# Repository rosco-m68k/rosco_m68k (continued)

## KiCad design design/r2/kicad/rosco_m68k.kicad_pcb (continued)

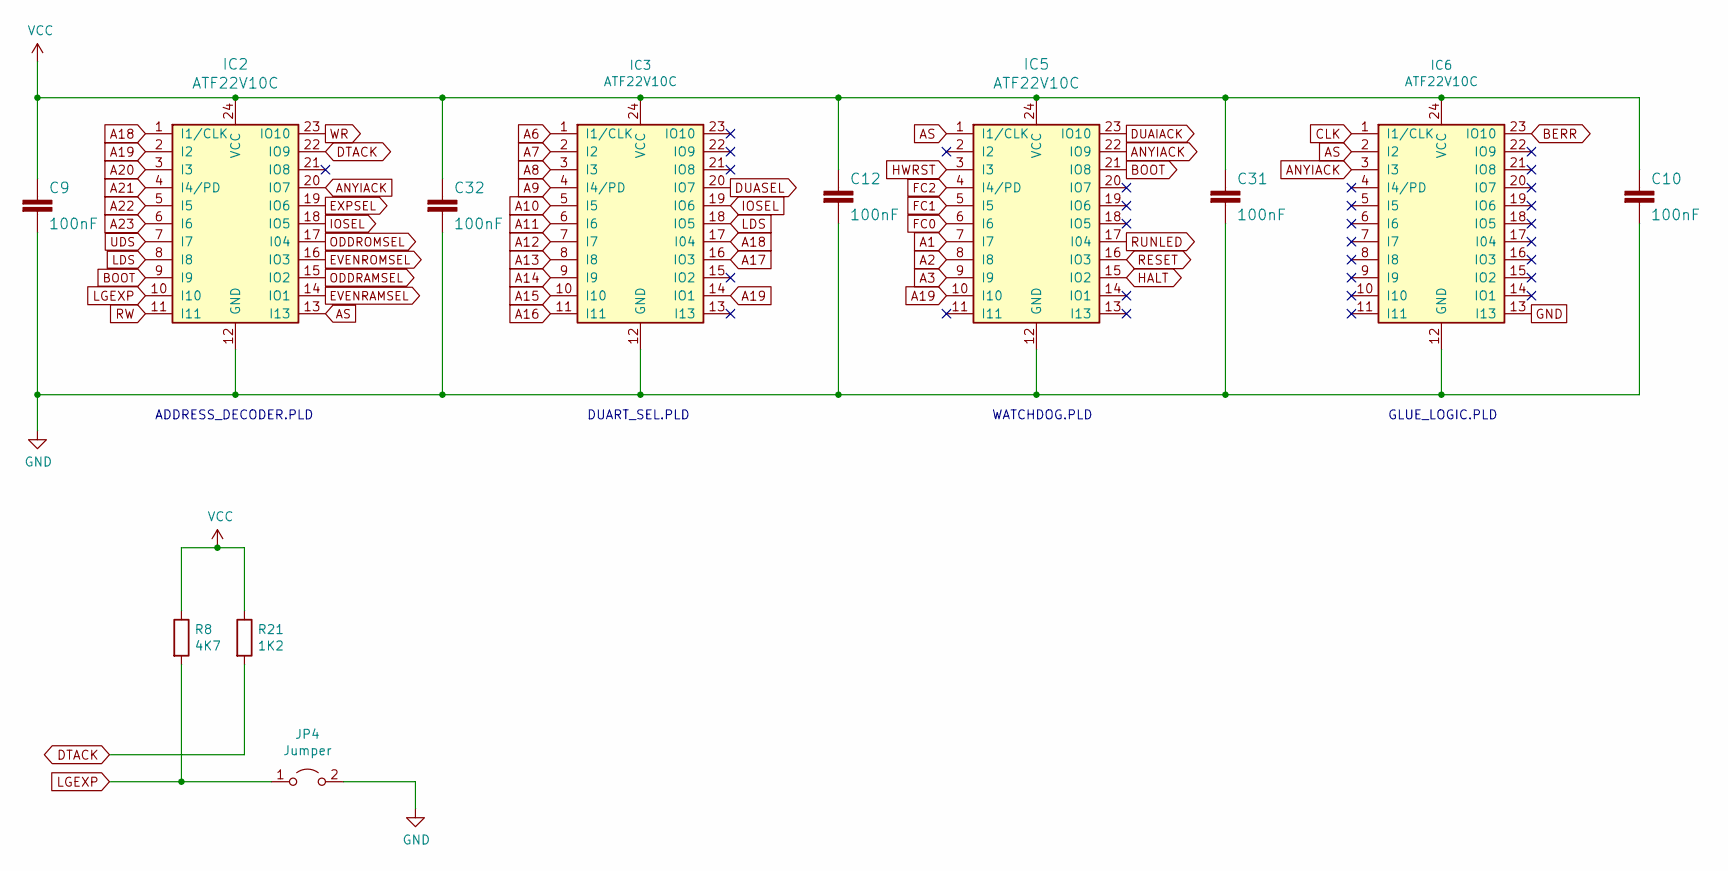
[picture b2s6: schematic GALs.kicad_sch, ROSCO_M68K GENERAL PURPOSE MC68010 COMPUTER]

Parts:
C9, C10, C12, C31, C32: 100nF; C2.5-3
IC2, IC3, IC5, IC6: ATF22V10C; DIP-24_W7.62mm_Socket_LongPads
JP4: Jumper; 1X02
R8: 4K7; 0207_10
R21: 1K2; 0207_10

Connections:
A1: IC5.7 (I7); also elsewhere on the board
A2: IC5.8 (I8); also elsewhere on the board
A3: IC5.9 (I9); also elsewhere on the board
A6: IC3.1 (I1/CLK); also elsewhere on the board
A7: IC3.2 (I2); also elsewhere on the board
A8: IC3.3 (I3); also elsewhere on the board
A9: IC3.4 (I4/PD); also elsewhere on the board
A10: IC3.5 (I5); also elsewhere on the board
A11: IC3.6 (I6); also elsewhere on the board
A12: IC3.7 (I7); also elsewhere on the board
A13: IC3.8 (I8); also elsewhere on the board
A14: IC3.9 (I9); also elsewhere on the board
A15: IC3.10 (I10); also elsewhere on the board
A16: IC3.11 (I11); also elsewhere on the board
A17: IC3.16 (IO3); also elsewhere on the board
A18: IC2.1 (I1/CLK), IC3.17 (I04); also elsewhere on the board
A19: IC2.2 (I2), IC3.14 (IO1), IC5.10 (I10); also elsewhere on the board
A20: IC2.3 (I3); also elsewhere on the board
A21: IC2.4 (I4/PD); also elsewhere on the board
A22: IC2.5 (I5); also elsewhere on the board
A23: IC2.6 (I6); also elsewhere on the board
ANYIACK: IC2.20 (IO7), IC5.22 (IO9), IC6.3 (I3)
AS: IC2.13 (I13), IC5.1 (I1/CLK), IC6.2 (I2); also elsewhere on the board
BERR: IC6.23 (IO10); also elsewhere on the board
BOOT: IC2.9 (I9), IC5.21 (IO8)
CLK: IC6.1 (I1/CLK); also elsewhere on the board
DTACK: IC2.22 (IO9), R21.2; also elsewhere on the board
DUAIACK: IC5.23 (IO10); also elsewhere on the board
DUASEL: IC3.20 (IO7); also elsewhere on the board
EVENRAMSEL: IC2.14 (IO1); also elsewhere on the board
EVENROMSEL: IC2.16 (IO3); also elsewhere on the board
EXPSEL: IC2.19 (IO6); also elsewhere on the board
FC0: IC5.6 (I6); also elsewhere on the board
FC1: IC5.5 (I5); also elsewhere on the board
FC2: IC5.4 (I4/PD); also elsewhere on the board
GND: C9.2, C10.2, C12.2, C31.2, C32.2, IC2.12 (GND), IC3.12 (GND), IC5.12 (GND), IC6.12 (GND), IC6.13 (I13), JP4.2 (B); also elsewhere on the board
HALT: IC5.15 (IO2); also elsewhere on the board
HWRST: IC5.3 (I3); also elsewhere on the board
IOSEL: IC2.18 (IO5), IC3.19 (IO6); also elsewhere on the board
LDS: IC2.8 (I8), IC3.18 (IO5); also elsewhere on the board
LGEXP: IC2.10 (I10), JP4.1 (A), R8.2
ODDRAMSEL: IC2.15 (IO2); also elsewhere on the board
ODDROMSEL: IC2.17 (I04); also elsewhere on the board
RESET: IC5.16 (IO3); also elsewhere on the board
RUNLED: IC5.17 (I04); also elsewhere on the board
RW: IC2.11 (I11); also elsewhere on the board
UDS: IC2.7 (I7); also elsewhere on the board
VCC: C9.1, C10.1, C12.1, C31.1, C32.1, IC2.24 (VCC), IC3.24 (VCC), IC5.24 (VCC), IC6.24 (VCC), R8.1, R21.1; also elsewhere on the board
WR: IC2.23 (IO10); also elsewhere on the board

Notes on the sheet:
GLUE_LOGIC.PLD
ADDRESS_DECODER.PLD
DUART_SEL.PLD
WATCHDOG.PLD

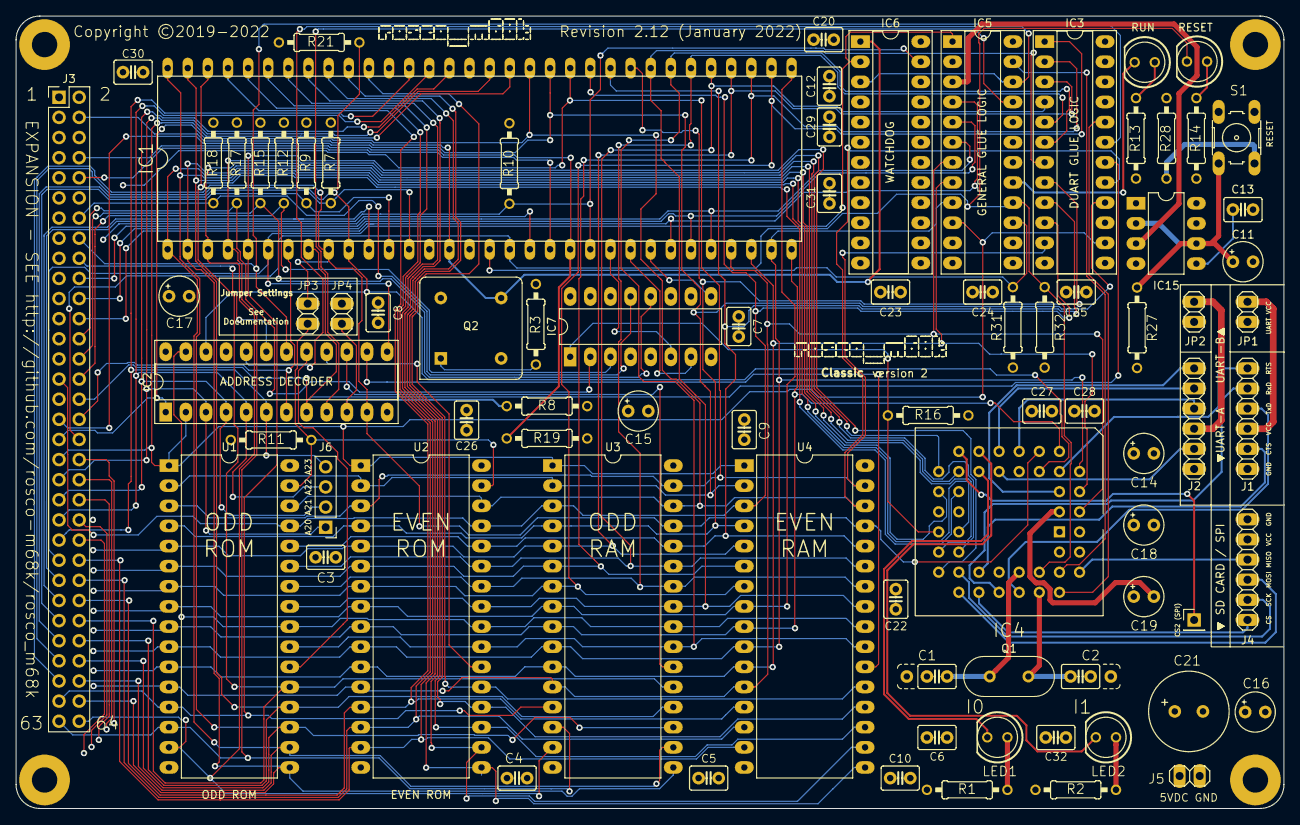
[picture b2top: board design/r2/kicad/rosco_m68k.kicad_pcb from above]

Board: 4 copper layers, 160.0 x 100.0 mm, 88 parts (0 on the bottom side), 109 nets.

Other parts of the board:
OSHW_Mono_0.25_Scale: UK000006; OSHW_Mono_0.25_Scale

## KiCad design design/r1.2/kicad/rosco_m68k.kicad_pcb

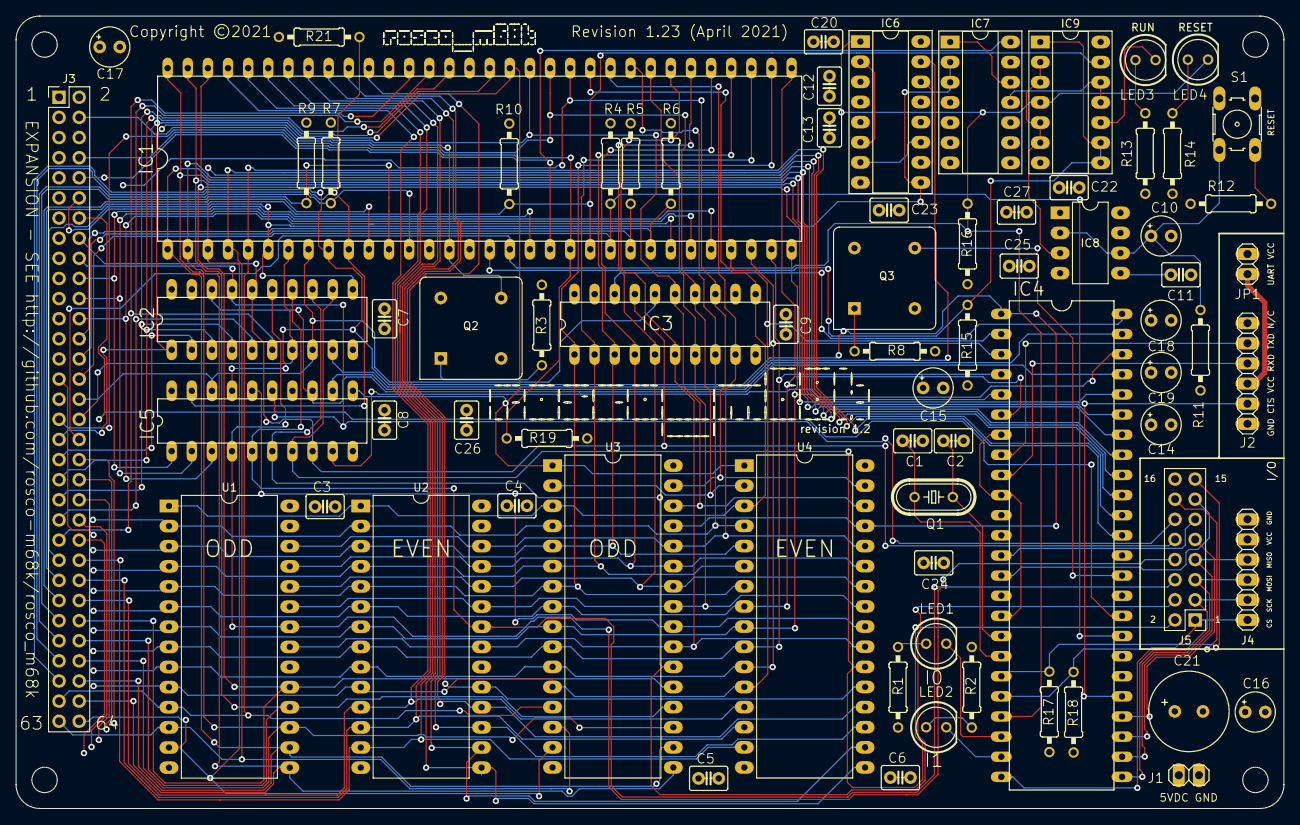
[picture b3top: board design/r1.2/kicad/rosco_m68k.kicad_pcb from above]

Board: 4 copper layers, 160.0 x 100.0 mm, 79 parts (0 on the bottom side), 110 nets.

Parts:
C1, C2: 33pF; C2.5-3
C3, C4, C5, C6, C7, C8, C9, C11, C12, C13, C20, C22, C23, C24, C25, C26, C27: 100nF; C2.5-3
C10, C14, C15, C16, C17, C18, C19: 100uF; E2,5-5
C21: 470uF; E3,5-10
H1, H2, H3, H4: MountingHole; MountingHole_3.2mm_M3
IC1: MC68010P10; DIL64
IC2, IC3, IC5: ATF16V8BQL-15PU; DIL20
IC4: MC68901P; DIL48
IC6: 74174N; DIP-16_W7.62mm_Socket_LongPads
IC7: 74LS93; DIP-14_W7.62mm_Socket_LongPads
IC8: 555N; DIP-8_W7.62mm_LongPads
IC9: 74LS01N; DIP-14_W7.62mm_Socket_LongPads
J1: PWR; 1X02
J2, J4: Conn_01x06; 1X06
J3: Conn_02x32_Odd_Even; PinHeader_2x32_P2.54mm_Vertical
J5: GPIO-PANEL; PinHeader_2x08_P2.54mm_Vertical
JP1: FTDI POWER; 1X02
LED1, LED3: GREEN; LED5MM
LED2, LED4: RED; LED5MM
OSHW_Mono_0.25_Scale: UK000006; OSHW_Mono_0.25_Scale
Q1: 3.6864MHz; HC49_S
Q2: 5H8ET-10.000; Oscillator_DIP-8
Q3: 5H8ET-4.000; Oscillator_DIP-8
R1, R2, R13, R14: 330R; 0207_10
R3, R4, R5, R6, R7, R8, R9, R10, R15, R16, R17, R18: 4K7; 0207_10
R11, R21: 2K2; 0207_10
R12: 270R; 0207_10
R19: 10K; 0207_10
S1: 10-XX; B3F-10XX
U1, U2: AT28C256-15PU; DIP-28_W15.24mm_LongPads
U3, U4: AS6C4008-55PCN; DIP-32_W15.24mm_LongPads

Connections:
/Expansion/A1: IC1.29, IC4.2, J3.1, U1.10, U2.10, U3.12, U4.12
/Expansion/A2: IC1.30, IC4.3, J3.3, U1.9, U2.9, U3.11, U4.11
/Expansion/A3: IC1.31, IC4.4, J3.5, U1.8, U2.8, U3.10, U4.10
/Expansion/A4: IC1.32, IC4.5, J3.7, U1.7, U2.7, U3.9, U4.9
/Expansion/A5: IC1.33, IC4.6, J3.9, U1.6, U2.6, U3.8, U4.8
/Expansion/A6: IC1.34, IC3.1, J3.11, U1.5, U2.5, U3.7, U4.7
/Expansion/A7: IC1.35, IC3.2, J3.13, U1.4, U2.4, U3.6, U4.6
/Expansion/A8: IC1.36, IC3.3, J3.15, U1.3, U2.3, U3.5, U4.5
/Expansion/A9: IC1.37, IC3.4, J3.17, U1.25, U2.25, U3.27, U4.27
/Expansion/A10: IC1.38, IC3.5, J3.19, U1.24, U2.24, U3.26, U4.26
/Expansion/A11: IC1.39, IC3.6, J3.21, U1.21, U2.21, U3.23, U4.23
/Expansion/A12: IC1.40, IC3.7, J3.23, U1.23, U2.23, U3.25, U4.25
/Expansion/A13: IC1.41, IC3.8, J3.25, U1.2, U2.2, U3.4, U4.4
/Expansion/A14: IC1.42, IC3.9, J3.27, U1.26, U2.26, U3.28, U4.28
/Expansion/A15: IC1.43, IC3.11, J3.29, U1.1, U2.1, U3.3, U4.3
/Expansion/A16: IC1.44, IC3.13, J3.31, U3.31, U4.31
/Expansion/A17: IC1.45, IC3.14, J3.33, U3.2, U4.2
/Expansion/A18: IC1.46, IC2.1, IC3.15, J3.35, U3.30, U4.30
/Expansion/A19: IC1.47, IC2.2, IC5.11, J3.37, U3.1, U4.1
/Expansion/A20: IC1.48, IC2.3, J3.39
/Expansion/A21: IC1.50, IC2.4, J3.41
/Expansion/A22: IC1.51, IC2.5, J3.43
/Expansion/A23: IC1.52, IC2.6, J3.45
/Expansion/D0: IC1.5, IC4.37, J3.61, U1.11, U3.13
/Expansion/D1: IC1.4, IC4.38, J3.63, U1.12, U3.14
/Expansion/D2: IC1.3, IC4.39, J3.64, U1.13, U3.15
/Expansion/D3: IC1.2, IC4.40, J3.62, U1.15, U3.17
/Expansion/D4: IC1.1, IC4.41, J3.60, U1.16, U3.18
/Expansion/D5: IC1.64, IC4.42, J3.58, U1.17, U3.19
/Expansion/D6: IC1.63, IC4.43, J3.56, U1.18, U3.20
/Expansion/D7: IC1.62, IC4.44, J3.54, U1.19, U3.21
/Expansion/D8: IC1.61, J3.52, U2.11, U4.13
/Expansion/D9: IC1.60, J3.50, U2.12, U4.14
/Expansion/D10: IC1.59, J3.48, U2.13, U4.15
/Expansion/D11: IC1.58, J3.46, U2.15, U4.17
/Expansion/D12: IC1.57, J3.44, U2.16, U4.18
/Expansion/D13: IC1.56, J3.42, U2.17, U4.19
/Expansion/D14: IC1.55, J3.40, U2.18, U4.20
/Expansion/D15: IC1.54, J3.38, U2.19, U4.21
/Main_Bus/UARTRX: IC4.9, J2.4
/Main_Bus/UARTTX: IC4.8, J2.5
AS: IC1.6, IC2.11, IC6.9, IC7.2, IC7.3, J3.47
BERR: IC1.22, IC9.13, J3.49, R10.1
BG: IC1.11, J3.51
BGACK: IC1.12, J3.53, R9.1
BOOT: IC2.9, IC6.15
BR: IC1.13, J3.55, R7.1
CLK: IC1.15, J3.4, Q2.5
DTACK: IC1.10, IC5.19, J3.57, R21.1
E: IC1.20, IC7.14, J3.10
EVENRAMSEL: IC2.12, IC5.7, J5.2, U4.22
EVENROMSEL: IC2.14, IC5.5, J5.6, U2.22
EXPSEL: IC2.17, IC5.15, J3.18, J5.12
FC0: IC1.28, IC5.1, J3.20
FC1: IC1.27, IC5.2, J3.22
FC2: IC1.26, IC5.3, J3.24
GND: C1.2, C2.2, C3.2, C4.2, C5.2, C6.2, C7.2, C8.2, C9.2, C10.-, C12.2, C13.2, C14.-, C15.-, C16.-, C17.-, C18.-, C19.-, C20.2, C21.-, C22.2, C23.2, C24.2, C25.2, C26.2, C27.2, IC1.16, IC1.53, IC2.10, IC3.10, IC4.34, IC4.36, IC5.10, IC6.4, IC6.8, IC6.13, IC7.10, IC8.1, IC9.7, J1.2, J2.1, J3.6, J4.6, J5.16, Q2.4, Q3.4, R12.1, R17.2, R18.2, U1.14, U1.20, U2.14, U2.20, U3.16, U4.16
GPIO1: IC4.24, J4.1, J5.1
GPIO2: IC4.25, J4.2, J5.3
GPIO3: IC4.26, J4.3, J5.5
GPIO4: IC4.27, J4.4, J5.7
GPIO5: IC4.28, J5.9
HALT: IC1.17, IC9.1, IC9.8, IC9.9, R15.1
IACK: IC2.18, IC4.45, IC5.13
IEO: IC4.33, J3.14
IODTACK: IC4.46, IC5.9
IOSEL: IC2.16, IC3.17, IC5.8, J3.16, J5.10
IPL0: IC1.25, J3.26, R6.1
IPL1: IC1.24, J3.28, R5.1
IPL2: IC1.23, IC4.32, J3.30, R4.1
LDS: IC1.8, IC2.8, IC3.16, IC5.18, J3.32
MFPCLK: IC4.35, Q3.5
MFPDS: IC4.47, IC5.12
MFPSEL: IC3.18, IC4.48
unnamed: C1.1, IC4.18, Q1.1
unnamed: C2.1, IC4.17, Q1.2
unnamed: C10.+, IC8.2, IC8.6, R11.1, S1.1
unnamed: C11.2, IC8.5
unnamed: IC4.7, IC4.10, IC4.16
unnamed: IC4.22, LED1.K
unnamed: IC4.23, LED2.K
unnamed: IC4.29, J2.2
unnamed: IC6.2, IC6.6
unnamed: IC6.10, IC6.14
unnamed: IC6.7, IC6.11
unnamed: IC7.1, IC7.12
unnamed: IC7.11, IC9.11, IC9.12
unnamed: IC8.3, IC9.2, IC9.3, IC9.5, IC9.6
unnamed: IC9.10, LED3.K
unnamed: J2.3, JP1.2
unnamed: LED1.A, R1.1
unnamed: LED2.A, R2.1
unnamed: LED3.A, R13.1
unnamed: LED4.A, R14.1
unnamed: Q2.1, R3.2
unnamed: Q3.1, R8.2
unnamed: R12.2, S1.3
ODDRAMSEL: IC2.13, IC5.6, J5.4, U3.22
ODDROMSEL: IC2.15, IC5.4, J5.8, U1.22
RAMOE: IC5.16, U3.24, U4.24
RESET: IC1.18, IC4.21, IC6.1, IC9.4, J3.36, LED4.K, R16.1
RW: IC1.9, IC4.1, IC5.17, J3.59, U3.29, U4.29
TAI: IC4.19, J5.15, R17.1
TAO: IC4.13, J5.11
TBI: IC4.20, J5.14, R18.1
TBO: IC4.14, J5.13
UDS: IC1.7, IC2.7, J3.34
VCC: C3.1, C4.1, C5.1, C6.1, C7.1, C8.1, C9.1, C11.1, C12.1, C13.1, C14.+, C15.+, C16.+, C17.+, C18.+, C19.+, C20.1, C21.+, C22.1, C23.1, C24.1, C25.1, C26.1, C27.1, IC1.14, IC1.49, IC2.20, IC3.20, IC4.11, IC5.20, IC6.3, IC6.16, IC7.5, IC8.4, IC8.8, IC9.14, J1.1, J3.2, J4.5, JP1.1, Q2.8, Q3.8, R1.2, R2.2, R3.1, R4.2, R5.2, R6.2, R7.2, R8.1, R9.2, R10.2, R11.2, R13.2, R14.2, R15.2, R16.2, R19.1, R21.2, U1.27, U1.28, U2.27, U2.28, U3.32, U4.32
VMA: IC1.19, J3.12
VPA: IC1.21, J3.8, R19.2

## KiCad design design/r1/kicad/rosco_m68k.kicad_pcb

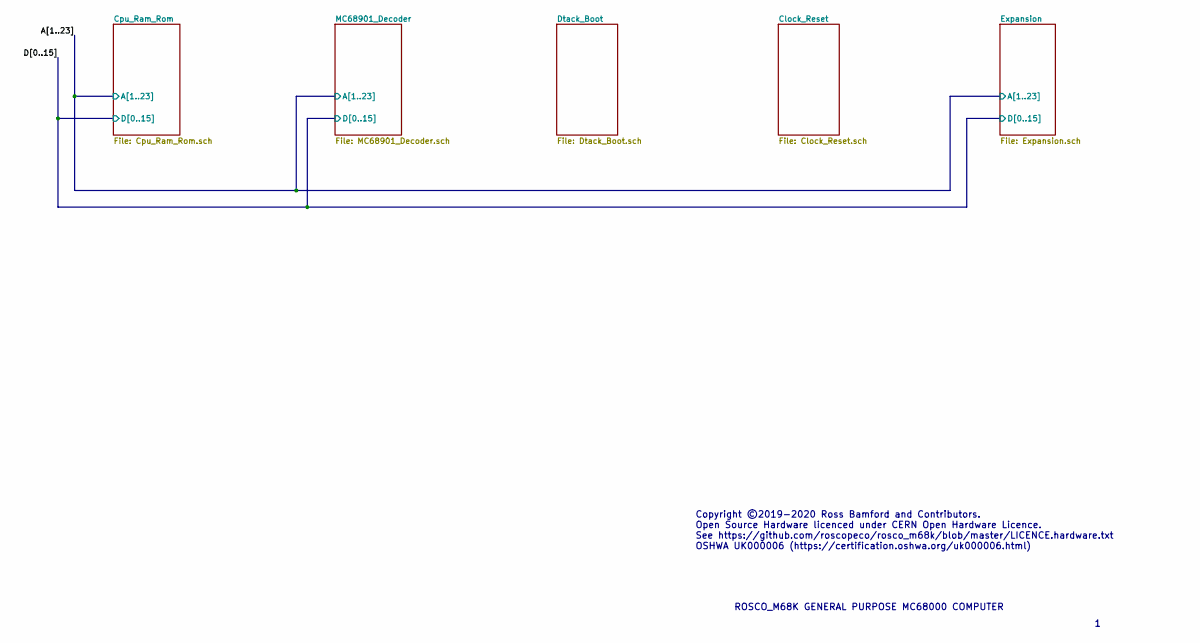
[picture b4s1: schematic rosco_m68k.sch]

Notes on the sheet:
Copyright ©2019-2020 Ross Bamford and Contributors. Open Source Hardware licenced under CERN Open Hardware Licence. See https://github.com/roscopeco/rosco_m68k/blob/master/LICENCE.hardware.txt OSHWA UK000006 (https://certification.oshwa.org/uk000006.html)
ROSCO_M68K GENERAL PURPOSE MC68000 COMPUTER

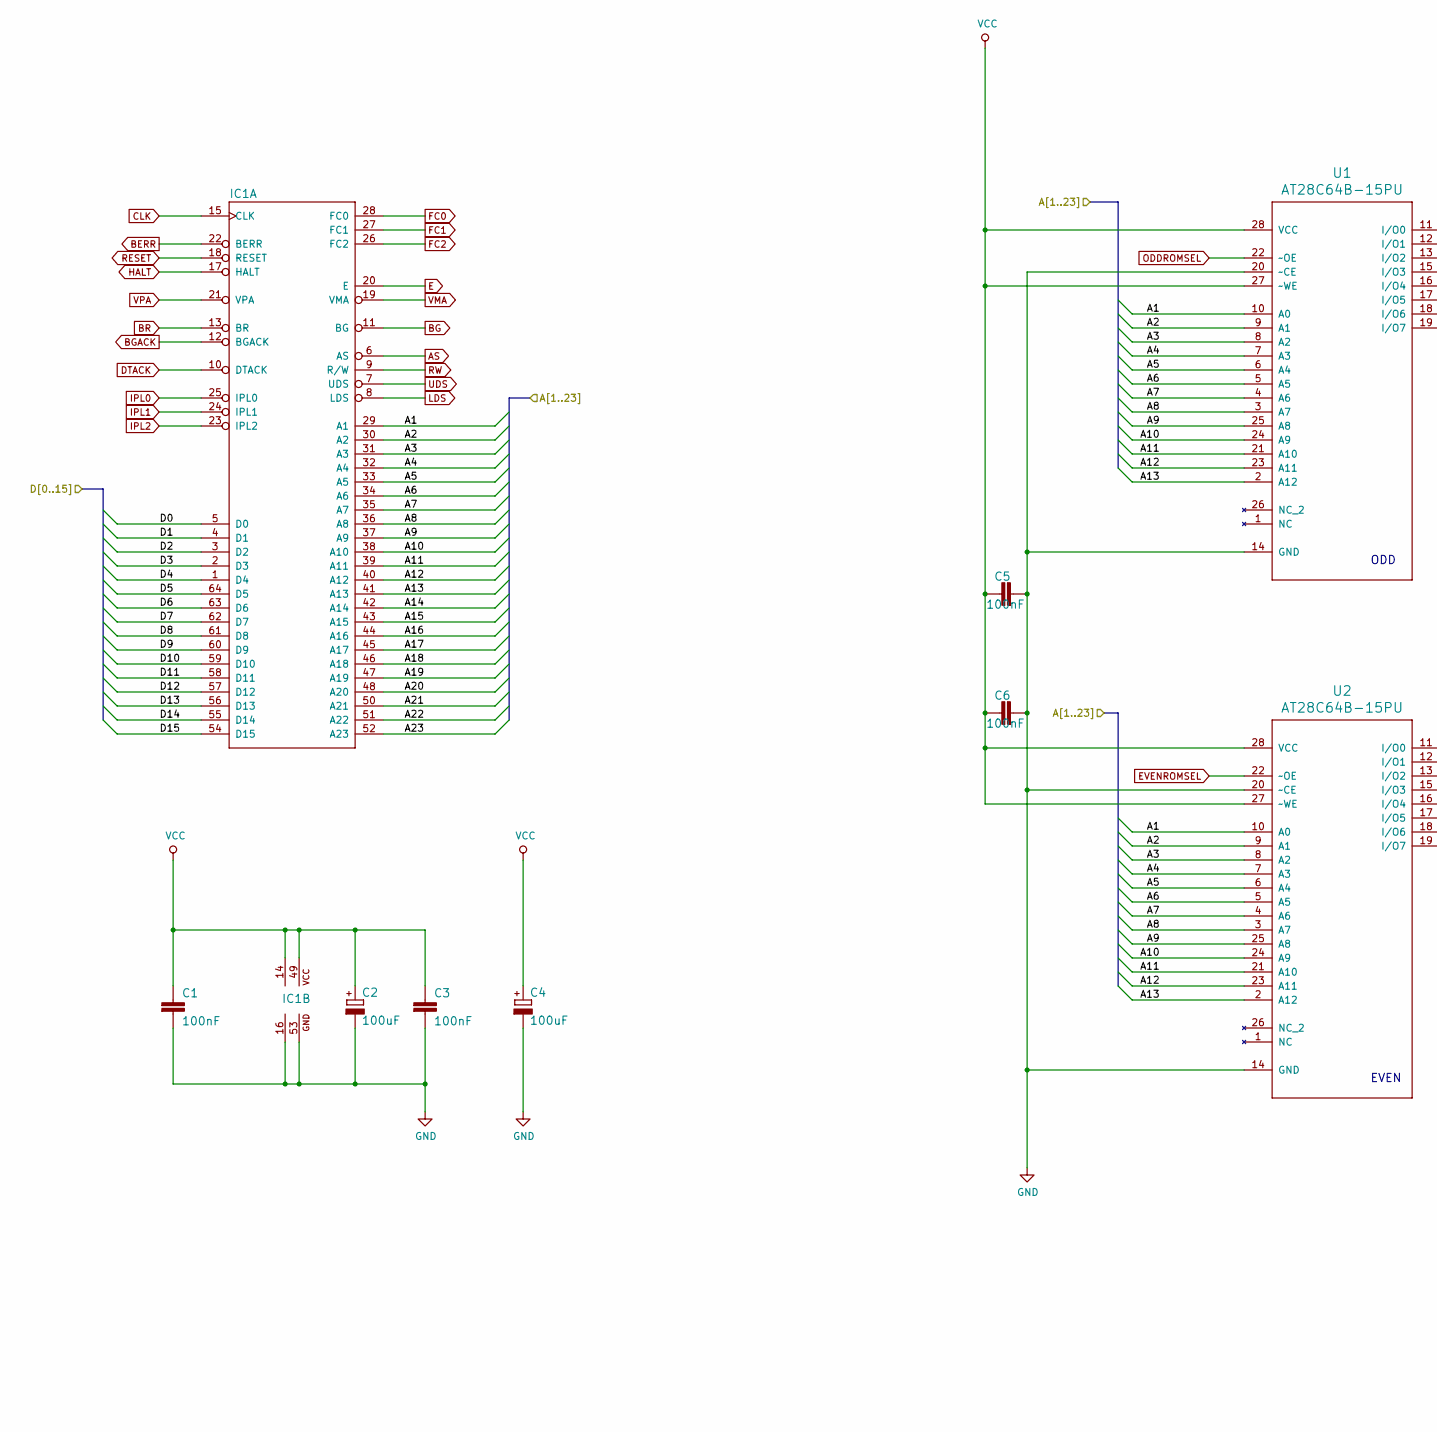
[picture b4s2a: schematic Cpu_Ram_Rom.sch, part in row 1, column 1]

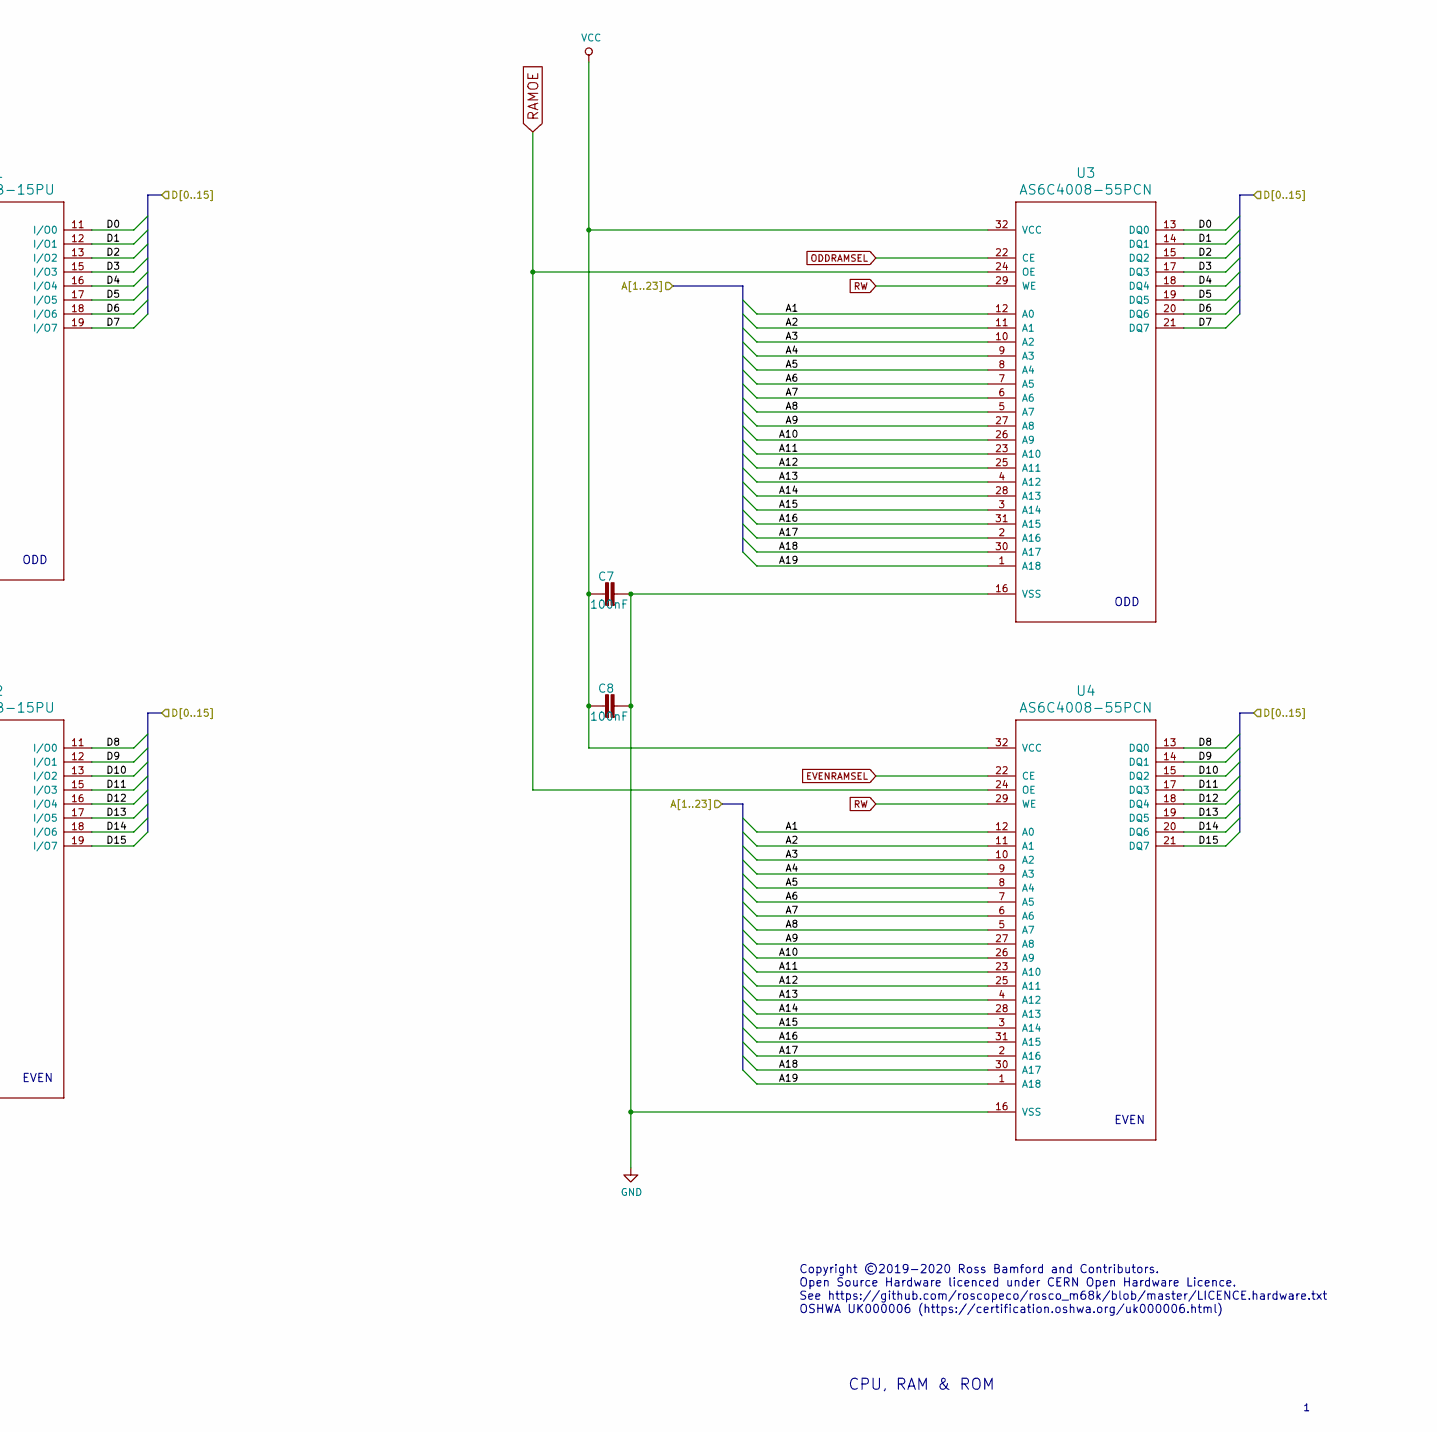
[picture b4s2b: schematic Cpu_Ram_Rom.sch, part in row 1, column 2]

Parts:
C1, C3, C5, C6, C7, C8: 100nF; C2.5-3
C2, C4: 100uF; E2,5-5
IC1: MC68010P10; DIL64
U1, U2: AT28C64B-15PU
U3, U4: AS6C4008-55PCN

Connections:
/Cpu_Ram_Rom/A1: IC1.29 (A1), U1.10 (A0), U2.10 (A0), U3.12 (A0), U4.12 (A0); also elsewhere on the board
/Cpu_Ram_Rom/A2: IC1.30 (A2), U1.9 (A1), U2.9 (A1), U3.11 (A1), U4.11 (A1); also elsewhere on the board
/Cpu_Ram_Rom/A3: IC1.31 (A3), U1.8 (A2), U2.8 (A2), U3.10 (A2), U4.10 (A2); also elsewhere on the board
/Cpu_Ram_Rom/A4: IC1.32 (A4), U1.7 (A3), U2.7 (A3), U3.9 (A3), U4.9 (A3); also elsewhere on the board
/Cpu_Ram_Rom/A5: IC1.33 (A5), U1.6 (A4), U2.6 (A4), U3.8 (A4), U4.8 (A4); also elsewhere on the board
/Cpu_Ram_Rom/A6: IC1.34 (A6), U1.5 (A5), U2.5 (A5), U3.7 (A5), U4.7 (A5); also elsewhere on the board
/Cpu_Ram_Rom/A7: IC1.35 (A7), U1.4 (A6), U2.4 (A6), U3.6 (A6), U4.6 (A6); also elsewhere on the board
/Cpu_Ram_Rom/A8: IC1.36 (A8), U1.3 (A7), U2.3 (A7), U3.5 (A7), U4.5 (A7); also elsewhere on the board
/Cpu_Ram_Rom/A9: IC1.37 (A9), U1.25 (A8), U2.25 (A8), U3.27 (A8), U4.27 (A8); also elsewhere on the board
/Cpu_Ram_Rom/A10: IC1.38 (A10), U1.24 (A9), U2.24 (A9), U3.26 (A9), U4.26 (A9); also elsewhere on the board
/Cpu_Ram_Rom/A11: IC1.39 (A11), U1.21 (A10), U2.21 (A10), U3.23 (A10), U4.23 (A10); also elsewhere on the board
/Cpu_Ram_Rom/A12: IC1.40 (A12), U1.23 (A11), U2.23 (A11), U3.25 (A11), U4.25 (A11); also elsewhere on the board
/Cpu_Ram_Rom/A13: IC1.41 (A13), U1.2 (A12), U2.2 (A12), U3.4 (A12), U4.4 (A12); also elsewhere on the board
/Cpu_Ram_Rom/A14: IC1.42 (A14), U3.28 (A13), U4.28 (A13); also elsewhere on the board
/Cpu_Ram_Rom/A15: IC1.43 (A15), U3.3 (A14), U4.3 (A14); also elsewhere on the board
/Cpu_Ram_Rom/A16: IC1.44 (A16), U3.31 (A15), U4.31 (A15); also elsewhere on the board
/Cpu_Ram_Rom/A17: IC1.45 (A17), U3.2 (A16), U4.2 (A16); also elsewhere on the board
/Cpu_Ram_Rom/A18: IC1.46 (A18), U3.30 (A17), U4.30 (A17); also elsewhere on the board
/Cpu_Ram_Rom/A19: IC1.47 (A19), U3.1 (A18), U4.1 (A18); also elsewhere on the board
/Cpu_Ram_Rom/A20: IC1.48 (A20); also elsewhere on the board
/Cpu_Ram_Rom/A21: IC1.50 (A21); also elsewhere on the board
/Cpu_Ram_Rom/A22: IC1.51 (A22); also elsewhere on the board
/Cpu_Ram_Rom/A23: IC1.52 (A23); also elsewhere on the board
/Cpu_Ram_Rom/D0: IC1.5 (D0), U1.11 (I/O0), U3.13 (DQ0); also elsewhere on the board
/Cpu_Ram_Rom/D1: IC1.4 (D1), U1.12 (I/O1), U3.14 (DQ1); also elsewhere on the board
/Cpu_Ram_Rom/D2: IC1.3 (D2), U1.13 (I/O2), U3.15 (DQ2); also elsewhere on the board
/Cpu_Ram_Rom/D3: IC1.2 (D3), U1.15 (I/O3), U3.17 (DQ3); also elsewhere on the board
/Cpu_Ram_Rom/D4: IC1.1 (D4), U1.16 (I/O4), U3.18 (DQ4); also elsewhere on the board
/Cpu_Ram_Rom/D5: IC1.64 (D5), U1.17 (I/O5), U3.19 (DQ5); also elsewhere on the board
/Cpu_Ram_Rom/D6: IC1.63 (D6), U1.18 (I/O6), U3.20 (DQ6); also elsewhere on the board
/Cpu_Ram_Rom/D7: IC1.62 (D7), U1.19 (I/O7), U3.21 (DQ7); also elsewhere on the board
/Cpu_Ram_Rom/D8: IC1.61 (D8), U2.11 (I/O0), U4.13 (DQ0); also elsewhere on the board
/Cpu_Ram_Rom/D9: IC1.60 (D9), U2.12 (I/O1), U4.14 (DQ1); also elsewhere on the board
/Cpu_Ram_Rom/D10: IC1.59 (D10), U2.13 (I/O2), U4.15 (DQ2); also elsewhere on the board
/Cpu_Ram_Rom/D11: IC1.58 (D11), U2.15 (I/O3), U4.17 (DQ3); also elsewhere on the board
/Cpu_Ram_Rom/D12: IC1.57 (D12), U2.16 (I/O4), U4.18 (DQ4); also elsewhere on the board
/Cpu_Ram_Rom/D13: IC1.56 (D13), U2.17 (I/O5), U4.19 (DQ5); also elsewhere on the board
/Cpu_Ram_Rom/D14: IC1.55 (D14), U2.18 (I/O6), U4.20 (DQ6); also elsewhere on the board
/Cpu_Ram_Rom/D15: IC1.54 (D15), U2.19 (I/O7), U4.21 (DQ7); also elsewhere on the board
AS: IC1.6 (AS); also elsewhere on the board
BERR: IC1.22 (BERR); also elsewhere on the board
BG: IC1.11 (BG); also elsewhere on the board
BGACK: IC1.12 (BGACK); also elsewhere on the board
BR: IC1.13 (BR); also elsewhere on the board
CLK: IC1.15 (CLK); also elsewhere on the board
DTACK: IC1.10 (DTACK); also elsewhere on the board
E: IC1.20 (E); also elsewhere on the board
EVENRAMSEL: U4.22 (CE); also elsewhere on the board
EVENROMSEL: U2.22 (~~OE); also elsewhere on the board
FC0: IC1.28 (FC0); also elsewhere on the board
FC1: IC1.27 (FC1); also elsewhere on the board
FC2: IC1.26 (FC2); also elsewhere on the board
GND: C1.2, C2.-, C3.2, C4.-, C5.2, C6.2, C7.2, C8.2, IC1.16 (GND@1), IC1.53 (GND@2), U1.14 (GND), U1.20 (~~CE), U2.14 (GND), U2.20 (~~CE), U3.16 (VSS), U4.16 (VSS); also elsewhere on the board
HALT: IC1.17 (HALT); also elsewhere on the board
IPL0: IC1.25 (IPL0); also elsewhere on the board
IPL1: IC1.24 (IPL1); also elsewhere on the board
IPL2: IC1.23 (IPL2); also elsewhere on the board
LDS: IC1.8 (LDS); also elsewhere on the board
ODDRAMSEL: U3.22 (CE); also elsewhere on the board
ODDROMSEL: U1.22 (~~OE); also elsewhere on the board
RAMOE: U3.24 (OE), U4.24 (OE); also elsewhere on the board
RESET: IC1.18 (RESET); also elsewhere on the board
RW: IC1.9 (R/W), U3.29 (WE), U4.29 (WE); also elsewhere on the board
UDS: IC1.7 (UDS); also elsewhere on the board
VCC: C1.1, C2.+, C3.1, C4.+, C5.1, C6.1, C7.1, C8.1, IC1.14 (VCC@1), IC1.49 (VCC@2), U1.27 (~~WE), U1.28 (VCC), U2.27 (~~WE), U2.28 (VCC), U3.32 (VCC), U4.32 (VCC); also elsewhere on the board
VMA: IC1.19 (VMA); also elsewhere on the board
VPA: IC1.21 (VPA); also elsewhere on the board

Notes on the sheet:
ODD
EVEN
CPU, RAM & ROM
Copyright ©2019-2020 Ross Bamford and Contributors. Open Source Hardware licenced under CERN Open Hardware Licence. See https://github.com/roscopeco/rosco_m68k/blob/master/LICENCE.hardware.txt OSHWA UK000006 (https://certification.oshwa.org/uk000006.html)

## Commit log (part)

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2023-09-29 Fix a buffer overflow in E-Kermit GCC throws a warning/error after changing some compile settings. If `aln` >= `SIZEBUFL`, `i` will be `SIZEBUFL` at the end of the loops. `sizebuf[i] = '\0'` will the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
2023-09-29 Remove some custom recipes in stage2
2023-09-29 Clean up variables and config in makefiles Also minimize the inclusion of stage1 headers from stage2 and do some other cleanup and fixes.
2023-09-29 Duplicate variable defaults to stage2
2023-09-29 Remove configuration from `config.mk`, decouple stage2
2023-09-29 Improve Updateflash ROM ID Error Message (#362)
    * Updateflash checks that manufacturer is SST
    Ensures that the flash devices aren't mistaken for a device by another
    manufacturer which uses the same device ID.
    * Add a more helpful device message to updateflash
    Having the flash write jumper not installed will cause the ROMs not to
    be identifiable by the software, leading to an inability to program.
2023-10-09 Squashed commit of the following:
    commit 6568b6beaf75071636ffe7bb0fcaa0c35afb091f
    Author: Thomas Jager <0xTJ@users.noreply.github.com>
    Date: Fri Sep 29 13:22:30 2023 -0400
    Improve Updateflash ROM ID Error Message (#362)
    * Updateflash checks that manufacturer is SST
    Ensures that the flash devices aren't mistaken for a device by another
2023-10-09 copy sdfat_menu.bin as ROSCODE1.BIN on SD card
2023-10-09 Entrypoint is at virtual address, not load address This allows the ELF E_ENTRY to be usable, because it doesn't trigger the initial copying.
2023-10-09 Enforce physical load address in physical mode
2023-10-09 Move Kmain type definition to a header Also move some function declarations related to loading to the same header. Some more cleanup could be done in the future to reduce the number of extern variabl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
2023-10-09 Move kermit buffers to unused memory
2023-10-09 Don't hardcode SP for stage2
2023-10-09 improved method to free SERIAL port vs killall :)
2023-10-10 remove -n from macos open (accumulates terminals)
2023-10-10 Fix for _kermit_end being non-inclusive
2023-10-11 Boot ELF Kernel from Storage (#365)
    * Allow using more than the minimal FAT API
    Needed to allow seeking.
    * Allow modifying the kernel entry point during load
    * Remove duplicate define
    * Preliminary ELF loading
    Seems to work, as long as the ELF file to load doesn't have segments
2023-10-22 Roll 2.5.dev
2023-10-22 Roll 2.5.dev release (#370)
2023-10-24 Ignore static libs
2023-10-24 Add <vector> include
2023-10-24 Revert "🤷 Try fix GITHUB_WORKSPACE thing [3]"
    This reverts commit 4369599145c125a8a3ae4daa409131a3e2088630.
2023-10-24 Test in CI, take 2 🤞
2023-10-26 Make program responsible for pmm setup
2023-10-27 Don't use impl-reserved ids
2023-10-28 Remove revision-specific defines from public Except for MFP, which is the only place that IOBASE was actually used
2023-10-28 Cleanup Outdated Equates (#377)
    * Remove equates.S
    * Remove revision-specific defines from public
    Except for MFP, which is the only place that IOBASE was actually used
    * Fix comment about equates.S
2023-10-28 Add CRC7 and 16 to SD Card routines
2023-10-29 Get it kinda working
2023-10-29 Handle TRAP15 the same as TRAP1
2023-10-29 Initial work on ctrl-c break into program
2023-10-29 fix frame struct refactor snafu
2023-10-29 More tidying up, still not figured out rerun 😭
2023-10-29 REVERT: temp test prog
2023-10-30 Update docs a bit
2023-10-30 Maybe fix ctrl-c interrupt stack handling
2023-10-31 Fix #359 (#378)
2023-10-31 Fix issues from PR
2023-11-07 Us FSINFO hints
2023-11-11 Initial work r2030 board
2023-11-11 Use reference instead of hardcoding
2023-11-18 Update README.md (#386)
2023-11-19 Switch default CPU to 68000
2023-11-19 Don't (ab)use SDB_STATUS for BERR_HANDLER return
2023-11-19 Consistently use INSTALL_TEMP_BERR_HANDLER
2023-11-28 Update r2 to Kicad 7
2023-11-28 Complete Kicad 7 migration
2023-12-01 Update typos in documentation
2023-12-02 Feature/kicad 7 (#388)
    * Update r2 to Kicad 7
    * Update r2020 to Kicad 7
    * Complete Kicad 7 migration
2023-12-05 Cleanup
2023-12-09 Align packed structs externally
2023-12-10 Swap TX/RX & CTS/RTS silkscreen r2020
    * Swap over labels
    * Add arrows
    * Some board tidy up
2023-12-10 Silkscreen fixes to match r2/r2020
2023-12-16 We've been lucky - it won't last. Fix it 😅
2023-12-16 Feature/fix weird kermit thing (#396)
    * We've been lucky - it won't last. Fix it 😅
    * Also include header
2023-12-17 Pack nested exception structs
2023-12-17 Use a Special Temporary BERR Handler for MC68000 (#397)
    * Always use helper routines
    * Use special temporary BERR handler for MC68000
    * Fix comment typo
2023-12-17 Tidy up for fab
2023-12-20 Only use SZ strings for multi-char sequences in ANSI console
2023-12-20 Remove duplicate serial.asm Stage2 has a copy of the serial.asm file present in stage1. Stage1 only uses RECVCHAR, which has the same pattern as the FW_* routines in trap14.asm. The FW_* EFP wrappers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
2023-12-20 Allow linker to specify memory top
2023-12-28 Fix incorrect number of 4k7s
2023-12-29 Add 030 information doc
2023-12-29 Bring r2 010 docs in line with new 020 docs
2024-01-01 Ignore KiCad lock files
2024-01-01 Fix RNs in BOM
2024-01-02 Feature/r2030 (#393)
    * Ignore bak
    * Initial work r2030 board
    * Silk fixes
    * Update for proto manufacturing
    * Update to Kicad 7
    * Fix pre-prod bugs
2024-01-02 Switch to defines for check/get input
2024-01-02 Support keyboard in sdfat_menu
2024-01-02 Add basic cache control to libs
2024-01-05 Address PR comments
2024-01-07 First cut keyboard support (#398)
    * First cut keyboard support
    * Support keyboard in sdfat_menu
    * Add missing define for check input
    * Switch to defines for check/get input
    * Support keyboard in memcheck
    * Address PR comments
2024-01-07 Fix master README notice
2024-01-07 Update release version notice
2024-01-07 Bring additions to firmware linker over to 64k
2024-01-13 Fix PR comments
2024-01-14 Update README.md
    Update to reflect JLCPCB are current for commercial boards.
2024-01-14 Update README.md (#407)
    Update to reflect JLCPCB are current for commercial boards.
2024-01-14 Add keyboard docs (#406)
    * Add keyboard docs
    * Address PR comment 😊
2024-01-25 Xosera ANSI term now overloading INPUTCHAR and CHECKINPUT
2024-01-26 Disable caches on warmboot
2024-01-27 Clear caches to avoid Sofowara FaFluru
    * Will avoid serious Dvsioi bybzere errors (observed in testing)
2024-01-28 Try keyboard input
2024-02-01 Restore use of BERR_CONT_ADDR in Xosera probing for 68000 use (#412)
2024-02-05 Add keyboard manual and errata
2024-02-06 Add NOP between INITMEMCOUNT write and read
2024-02-11 Feature/keyboard commercial docs (#413)
    * Remove outdated keyboard info
    * Add keyboard manual and errata
2024-02-20 Put common ld script parts in a common file
2024-02-20 Tweak stage2 ld script
2024-02-20 Fix incorrect EFPT offset in ld script
2024-02-20 Make zip unsigned char This has no effect, but figured it made sense for predictability.
2024-02-20 Don't assume that .data LMA is right after text
2024-02-27 Round updateflash half_size up Avoid missing the last byte when programming an odd-size image
2024-03-09 Minor classic refresh for 2024
    * Add DC jack
    * Silk cleanup
    * Unify added memory expansion headers
    * Minor routing cleanup
    * QR code on silk
2024-03-10 Minor classic refresh for 2024 (#416)
    * Minor classic refresh for 2024
    * Add DC jack
    * Silk cleanup
    * Unify added memory expansion headers
    * Minor routing cleanup
    * QR code on silk
2024-03-17 Update designs for copro GAL change
2024-03-17 Re-add mistakenly-removed polarity symbols
2024-03-18 Don't put debug_dump data below SP
2024-03-18 Load debug_stub fault address according to format
2024-03-21 Write to correct registers when setting red LED
2024-03-21 Change MFP use of SDB_SYSFLAGS, don't clear pins with system-use flag cleared
2024-03-22 More address lines into GALs
2024-04-05 prod
2024-04-07 Fix #422
2024-04-07 Fix debug trap handler beyond MC68010 (#418)
    * Don't put debug_dump data below SP
    * Use A6 as pointer to exception stack frame
    * Load debug_stub fault address according to format
    * Update copyright year
    * Propagate debug_stub changes to r68k and libs
    ---------
2024-04-07 Update designators to RUN/RESET in current BOMs
2024-04-07 Remove references to 'GPIO'
2024-04-15 Mask expansion and silk tidy after first spin
2024-04-23 Use a top-level Makefile to assemble stage1 and stage2
2024-04-23 Rename stage2 entry point to STAGE2_START
2024-04-25 Move some common Makefile lines into a central shared file
2024-04-26 Undo change to CPU options
2024-05-13 Clean up included Makefiles
2024-05-13 Add GCC 14 to param=min-pagesize=0
2024-05-14 Feature/smd birdseed (#427)
    * GAL changes to better support coprocessor
    * Update designs for copro GAL change
    * Revert accidental DUARTSEL changes
    * Re-add mistakenly-removed polarity symbols
    * Tentative r2 SMD design
    * Resize tiny resistors
2024-05-20 Fix leftover D3 spur
2024-05-20 Add r2.2 docs
2024-05-20 Also update fus and jed files
2024-05-20 PR fix
2024-05-22 Fix mame target in fw
2024-06-02 Fall through in EFPT C wrappers instead of branching
2024-06-08 Link stage2 against stage1 (#432)
    * Move stage1code into subdirectory
    * Use a top-level Makefile to assemble stage1 and stage2
    * Actually link stage2 against stage1 symbols, remove duped math
    * Remove stage2/machine.asm
    * Rename stage2 entry point to STAGE2_START
    * Clean up Makefiles
2024-06-18 Update 2.2 docs
2024-06-26 Update 2.2 docs (#433)
    * Update 2.2 docs
    * Remove eliminated C16
2024-07-21 Document MAME serial terminal
2024-07-27 Document MAME serial terminal (#436)
    * Document MAME serial terminal
    * Add success image
    * PR fix
2024-08-04 Fix an issue whereby we stomped .early_data which broke character devices (#440)
2024-08-04 Pin MicroPython core to v1.23.0
2024-08-04 Switch to new toolchain
2024-08-04 Add rosco_m68k micropython port
2024-08-04 Replace FAT12 with littlefs
2024-08-04 Split romfs support out a bit, move to newlib later
2024-08-04 Hook up 720KB ROMFS for 1MB ROM
2024-08-04 Remove Xosera submodule
2024-08-04 Make menu work
2024-08-04 Fix, then deprecate, ROM kernel
2024-08-04 Don't print video banner
2024-08-04 Make it autodetect both r1 Xosera and XoseRAM
2024-08-04 Enable 5sec timer
2024-08-04 Submods in pipeline
2024-08-04 Submods in pipeline, take 2
2024-08-04 Install xxd in build
2024-08-04 Revert "Install xxd in build"
    This reverts commit 10acd52168825b3cae3ba8441ace8dd14ca9db9c.
2024-08-04 Support audio in splash
2024-08-05 Integrate Xark's rect drawing fixes
2024-08-05 Re-enable blitter wait hack for now
2024-08-07 xwait_blit_ready before touching blitter
2024-08-08 firmware/trap14.asm: Add RECVCHAR for FC == 17.
2024-08-20 PR comments
2024-08-20 Feature/concept 2.5 (#435)
    * Add micropython core
    * Pin MicroPython core to v1.23.0
    * Switch to new toolchain
    * Add micropython submodule
    * Pin MP to v1.23.0
    * Add rosco_m68k micropython port
2024-09-06 r68k firmware: added #17 INPUTCHAR and #18 CHECKINPUT (#442)
    * firmware/trap14.asm: Add RECVCHAR for FC == 17.
    * firmware/trap14.asm: fixed up comment and added FC #18.
    ---------
    Authored-by: Warren Toomey <wkt@tuhs.org>
    Approved-by: Ross Bamford <roscopeco@gmail.com>
2024-10-02 skip splash if UART A input and exit loader to kermit upload if key was `k`
2024-10-04 Docs sept2024 update
2024-10-04 Build smaller flash ROMs in CI
2024-10-05 Remove sysconfig from menus for now
2024-10-06 Add dir traversal to SD demo
2024-10-06 Add evolution
2024-10-06 Try tables?
2024-10-06 Build smaller flash ROMs in CI (#452)
    * Build smaller flash ROMs in CI
    * Fix ROMDEVICE ids :D
2024-10-08 Try change based on PR comment
2024-10-08 Fix #448 (#458)
2024-10-08 Update toolchain docs
2024-10-09 WIP: Feature/remove bare metal toolchain dependency (#454)
    * Final removal of bare-metal toolchain dependencies
    * Update toolchain docs
2024-10-11 First PoC CH559 HID
2024-10-26 MAME can't support PMOVE MMUSP, use TC instead
2024-10-26 Fix build error in libs with gcc 13 due to libm maybe-uninitialized variable (#463)
2024-12-24 Add FW_CHECKINPUT and clear input buffer before debug_stub keypress wait
2025-02-19 Remove store link
2025-03-08 Upgrade actions/upload-artifact to non-removed v4
2025-04-06 Wait for a keypress at the end of `debug_stub` (#470)
    * Call FW_INPUTCHAR at the end of debug_stub
    * Add FW_CHECKINPUT and clear input buffer before debug_stub keypress wait
2025-04-14 Properly clear long-word D0 in CPUTYPE '000 check
2025-04-25 Move ROMFS to offset 0x40000 in flash
2025-05-31 Add in getting started infor from website to readme as markdown files
2025-06-07 Fix typo in PRINTCHAR description
2025-06-07 Fix typo in PRINTCHAR description (#482)
2026-03-11 feat: adds filename option and translate to text
